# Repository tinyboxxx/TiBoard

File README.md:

# TiBoard
>  TiBoard的硬件部分及说明文件

- merged SofleKeyboard and nrfBoard
- reserved place for trackpoint
- position of keys moved to my hand measurements
- carbon fiber top plate
- Voronoi style 3D print keycap

打包的KiCAD如果有什么问题麻烦发issue。

## 许可

可以自己随便做着玩。

空板交易无所谓，不要闲鱼卖套件，不要卖成品。

转载和修改版请带上我的名字。

## 需要注意购买的零件

**注意：为单套，左右手两只的数量需要x2 ！**

| 项目                 | 备注                                                         | 数量（单个板） | 链接                                                         |
| -------------------- | ------------------------------------------------------------ | -------------- | ------------------------------------------------------------ |
| E73蓝牙模块（PCB内） | E73-2G4M08S1C                                                | 1              | https://m.tb.cn/h.UL6DjRC  亿佰特nRF52840/52833芯片无线蓝牙MESH模块BLE4.2/5.0陶瓷天线 |
| 锂电池               | 402030（长30宽20厚4）不一定非要这家店，同尺寸带保护板即可。  | 1              | https://m.tb.cn/h.Upcs7Os  伯朗 导航行车记录仪锂电池大容量通用3.7v聚合物 |
| 轴体                 | 必须凯华1350型号，颜色任选                                   | 30             | https://m.tb.cn/h.UK0Awu7  凯华Kailh 1350巧克力机械键盘轴体  |
| 轴体热插拔底座       | 必须凯华1350型号                                             | 30             | https://item.taobao.com/item.htm?id=667154671807             |
| 定位板               | 厚度1.2mm，dxf文件见附件，参考价格碳纤维RMB68两片。也可以使用玻纤等其他不导电材料。 | 1              | https://item.taobao.com/item.htm?id=40340403528              |

## 状态及已知问题

BOM里充电电流设定用的R9 现在用的是2.2K，二极管是1N4148WS。

有其他疑问也请发issue。

已知问题：

- 目前使用的电池功耗大约1至2天，建议随时充电。
- 键位比较少 符号和其他按键不大方便。
- reset按钮位置比较难按。
- USB Type-C接口没有做沉板，左手的接口比较靠近桌子。
- 电池接插件比较大，目前直接焊线。
- I2C的两个电阻实测可以不焊接。
- 烧录E73模块真的很麻烦，需要先刷ST-LINK的固件 或者用STM32
- 指点杆的安装比较麻烦，而且可能影响厚度，兼容性还未测试。

## 链接

固件 https://github.com/tinyboxxx/zmk-config

固件下载 https://github.com/tinyboxxx/zmk-config/actions

键位编辑器 [ZMK Keymap Editor (nickcoutsos.github.io)](https://nickcoutsos.github.io/keymap-editor/)

视频 https://www.bilibili.com/video/BV1qe4y1t7zE/

烧录bootloader https://github.com/joric/nrfmicro/wiki/Bootloader#nrf52840

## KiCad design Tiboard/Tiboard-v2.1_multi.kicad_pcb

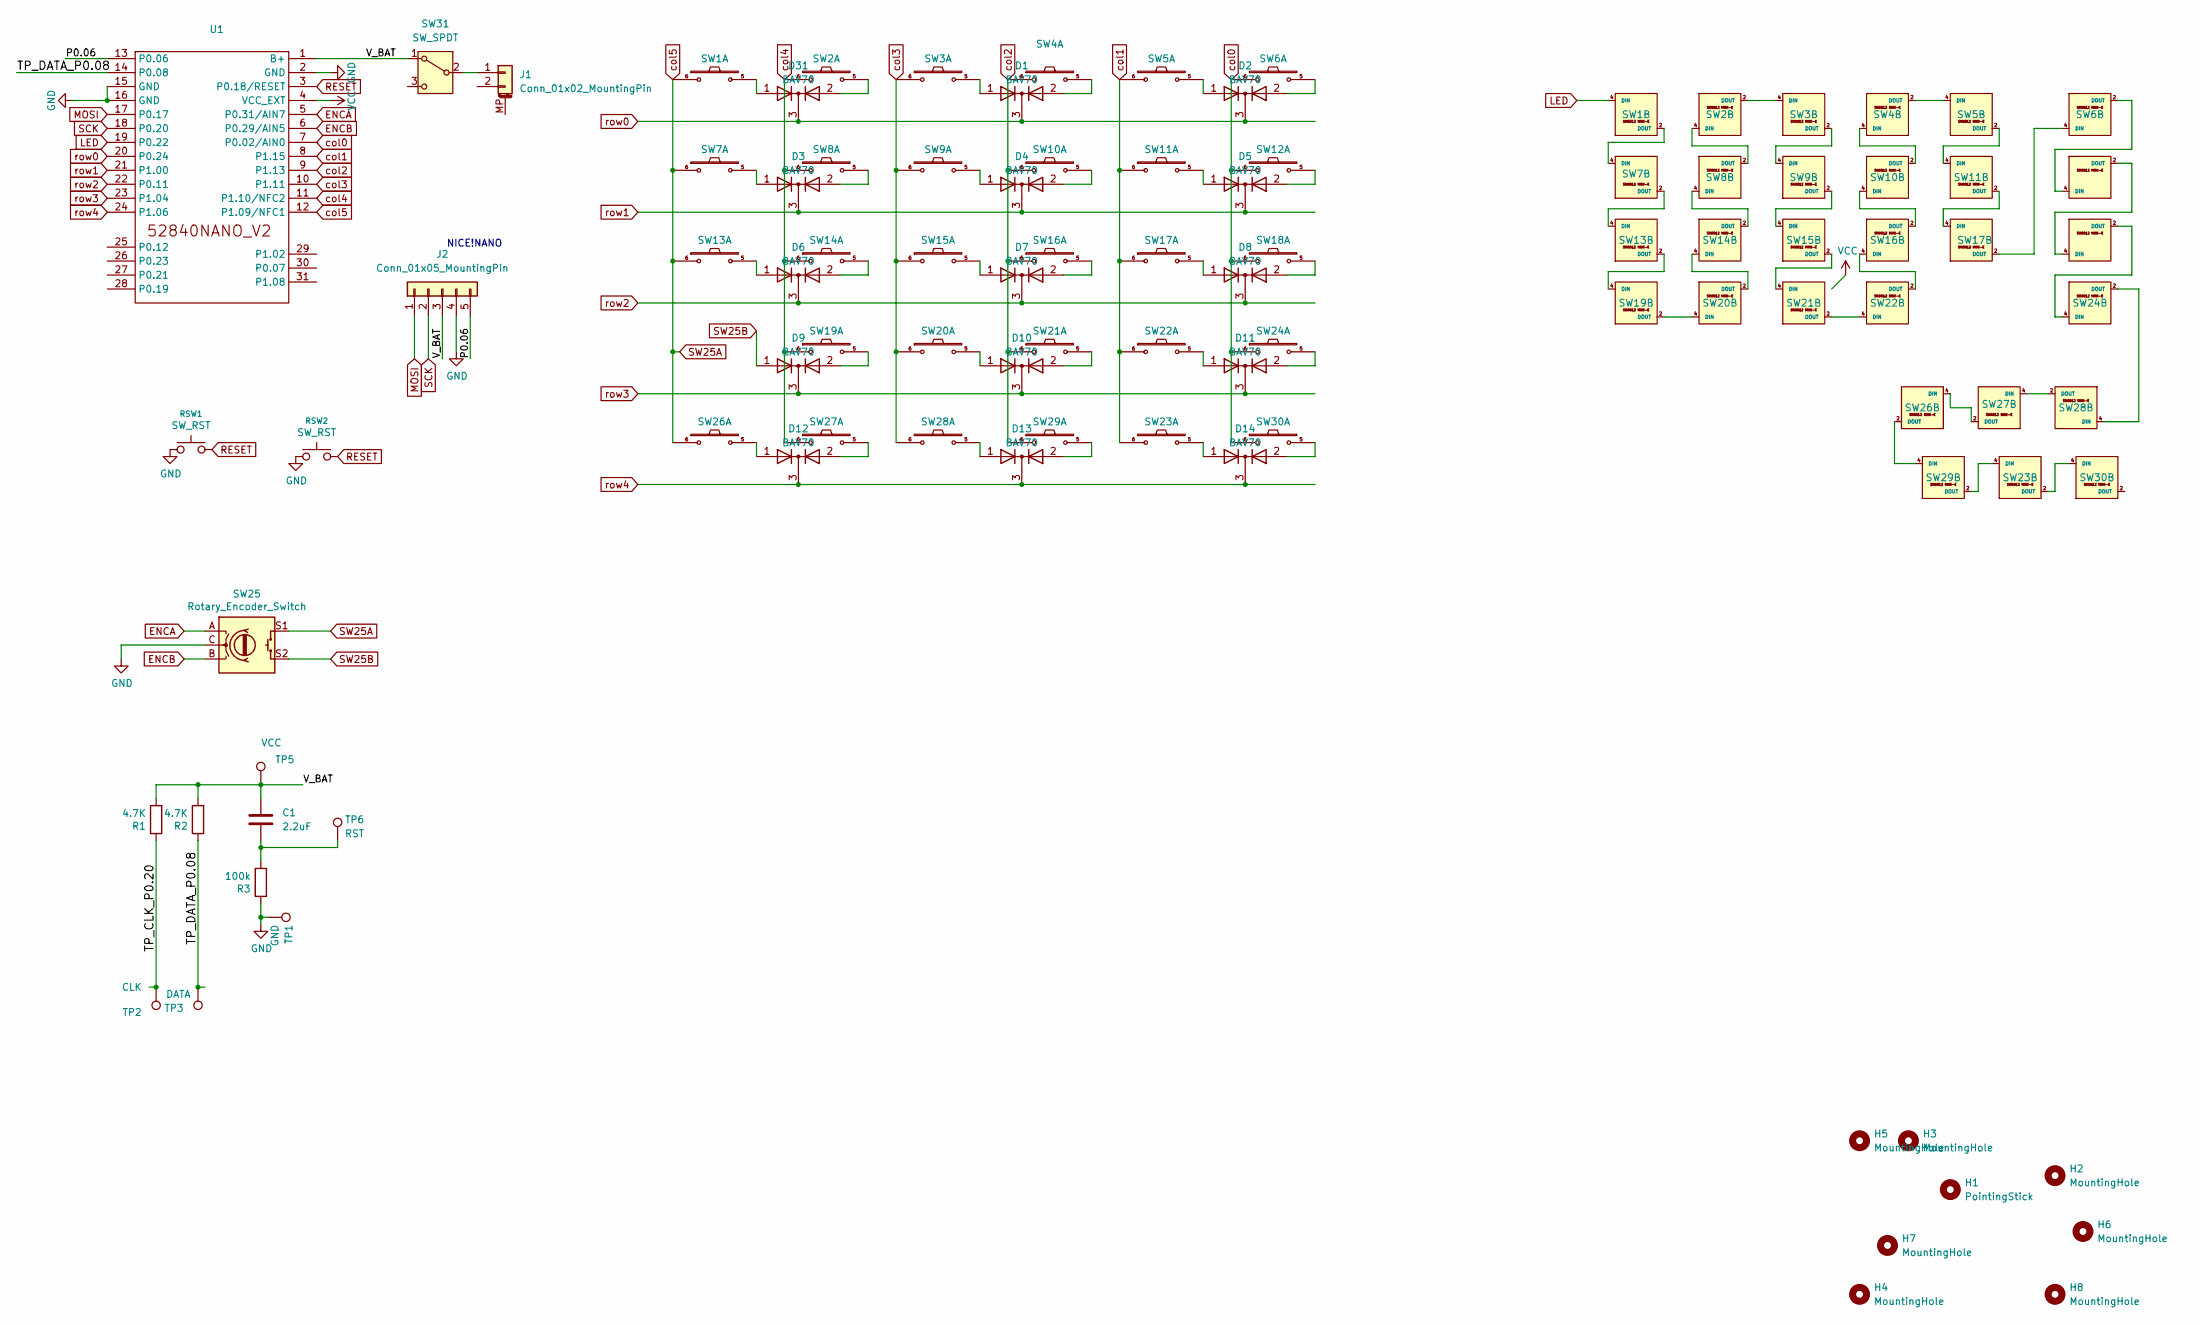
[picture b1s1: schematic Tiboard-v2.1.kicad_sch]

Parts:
C1: 2.2uF; C_0603_1608Metric
D1, D2, D3, D4, D5, D6, D7, D8, D9, D10, D11, D12, D13, D14, D31: BAV70; SOT-23
H1: PointingStick; Pointing_Stick
H2, H3, H4, H5, H6, H7, H8: MountingHole; MountingHole_3.2mm_M3_Pad_Via
J1: Conn_01x02_MountingPin; JST_SHL_SM02B-SHLS-TF_1x02-1MP_P1.00mm_Horizontal
J2: Conn_01x05_MountingPin; NICEVIEW_5Pin
R1, R2: 4.7K; R_0603_1608Metric
R3: 100k; R_0603_1608Metric
RSW1, RSW2: SW_RST; SW_SPST_CK_KXT3
SW1, SW2, SW3, SW4, SW5, SW6, SW7, SW8, SW9, SW10, SW11, SW12, SW13, SW14, SW15, SW16, SW17, SW18, SW19, SW20, SW21, SW22, SW23, SW24, SW26, SW27, SW28, SW29, SW30: SW_PUSH_LED; TTC_mini
SW25: Rotary_Encoder_Switch; RotaryEncoder_Alps_EC11E-Switch_Vertical_H20mm-keebio_modif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
SW31: SW_SPDT; SW_Slide_SPDT_Angled_CK_OS102011MA1Q
TP1: GND; TestPoint_Pad_1.0x1.0mm
TP2: CLK; TestPoint_Pad_1.0x1.0mm
TP3: DATA; TestPoint_Pad_1.0x1.0mm
TP5: VCC; TestPoint_Pad_1.0x1.0mm
TP6: RST; TestPoint_Pad_1.0x1.0mm
U1: 52840NANO_V2

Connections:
/P0.06: J2.5, U1.13 (P0.06)
ENCA: SW25.A, U1.5 (P0.31/AIN7)
ENCB: SW25.B, U1.6 (P0.29/AIN5)
LED: SW1.4 (DIN), U1.19 (P0.22)
unnamed: C1.2, R3.2, TP6.1
unnamed: D1.1 (A), SW3.5
unnamed: D1.2 (A), SW4.5
unnamed: D2.1 (A), SW5.5
unnamed: D2.2 (A), SW6.5
unnamed: D3.1 (A), SW7.5
unnamed: D3.2 (A), SW8.5
unnamed: D4.1 (A), SW9.5
unnamed: D4.2 (A), SW10.5
unnamed: D5.1 (A), SW11.5
unnamed: D5.2 (A), SW12.5
unnamed: D6.1 (A), SW13.5
unnamed: D6.2 (A), SW14.5
unnamed: D7.1 (A), SW15.5
unnamed: D7.2 (A), SW16.5
unnamed: D8.1 (A), SW17.5
unnamed: D8.2 (A), SW18.5
unnamed: D9.2 (A), SW19.5
unnamed: D10.1 (A), SW20.5
unnamed: D10.2 (A), SW21.5
unnamed: D11.1 (A), SW22.5
unnamed: D11.2 (A), SW24.5
unnamed: D12.1 (A), SW26.5
unnamed: D12.2 (A), SW27.5
unnamed: D13.1 (A), SW28.5
unnamed: D13.2 (A), SW29.5
unnamed: D14.1 (A), SW23.5
unnamed: D14.2 (A), SW30.5
unnamed: D31.1 (A), SW1.5
unnamed: D31.2 (A), SW2.5
unnamed: J1.1, SW31.2 (B)
unnamed: SW1.2 (DOUT), SW7.4 (DIN)
unnamed: SW2.4 (DIN), SW8.2 (DOUT)
unnamed: SW2.2 (DOUT), SW3.4 (DIN)
unnamed: SW3.2 (DOUT), SW9.4 (DIN)
unnamed: SW4.2 (DOUT), SW5.4 (DIN)
unnamed: SW10.4 (DIN), SW16.2 (DOUT)
unnamed: SW4.4 (DIN), SW10.2 (DOUT)
unnamed: SW5.2 (DOUT), SW11.4 (DIN)
unnamed: SW11.2 (DOUT), SW17.4 (DIN)
unnamed: SW6.2 (DOUT), SW12.4 (DIN)
unnamed: SW12.2 (DOUT), SW18.4 (DIN)
unnamed: SW7.2 (DOUT), SW13.4 (DIN)
unnamed: SW13.2 (DOUT), SW19.4 (DIN)
unnamed: SW14.4 (DIN), SW20.2 (DOUT)
unnamed: SW8.4 (DIN), SW14.2 (DOUT)
unnamed: SW9.2 (DOUT), SW15.4 (DIN)
unnamed: SW15.2 (DOUT), SW21.4 (DIN)
unnamed: SW16.4 (DIN), SW22.2 (DOUT)
unnamed: SW6.4 (DIN), SW17.2 (DOUT)
unnamed: SW18.2 (DOUT), SW24.4 (DIN)
unnamed: SW19.2 (DOUT), SW20.4 (DIN)
unnamed: SW21.2 (DOUT), SW22.4 (DIN)
unnamed: SW23.4 (DIN), SW29.2 (DOUT)
unnamed: SW23.2 (DOUT), SW30.4 (DIN)
unnamed: SW24.2 (DOUT), SW28.4 (DIN)
unnamed: SW26.4 (DIN), SW27.2 (DOUT)
unnamed: SW26.2 (DOUT), SW29.4 (DIN)
unnamed: SW27.4 (DIN), SW28.2 (DOUT)
RESET: RSW1.2, RSW2.2, U1.3 (P0.18/RESET)
SCL: J2.2, U1.18 (P0.20)
SDA: J2.1, U1.17 (P0.17)
SW25A: SW1.6, SW7.6, SW13.6, SW25.S1, SW26.6, U1.12 (P1.09/NFC1)
SW25B: D9.1 (A), SW25.S2
VCC: SW1.1 (VDD), SW2.1 (VDD), SW3.1 (VDD), SW4.1 (VDD), SW5.1 (VDD), SW6.1 (VDD), SW7.1 (VDD), SW8.1 (VDD), SW9.1 (VDD), SW10.1 (VDD), SW11.1 (VDD), SW12.1 (VDD), SW13.1 (VDD), SW14.1 (VDD), SW15.1 (VDD), SW16.1 (VDD), SW17.1 (VDD), SW18.1 (VDD), SW19.1 (VDD), SW20.1 (VDD), SW21.1 (VDD), SW22.1 (VDD), SW23.1 (VDD), SW24.1 (VDD), SW26.1 (VDD), SW27.1 (VDD), SW28.1 (VDD), SW29.1 (VDD), SW30.1 (VDD), U1.4 (VCC_EXT)
col0: SW6.6, SW12.6, SW18.6, SW24.6, SW30.6, U1.7 (P0.02/AIN0)
col1: SW5.6, SW11.6, SW17.6, SW22.6, SW23.6, U1.8 (P1.15)
col2: SW4.6, SW10.6, SW16.6, SW21.6, SW29.6, U1.9 (P1.13)
col3: SW3.6, SW9.6, SW15.6, SW20.6, SW28.6, U1.10 (P1.11)
col4: SW2.6, SW8.6, SW14.6, SW19.6, SW27.6, U1.11 (P1.10/NFC2)
row0: D1.3 (K), D2.3 (K), D31.3 (K), U1.20 (P0.24)
row1: D3.3 (K), D4.3 (K), D5.3 (K), U1.21 (P1.00)
row2: D6.3 (K), D7.3 (K), D8.3 (K), U1.22 (P0.11)
row3: D9.3 (K), D10.3 (K), D11.3 (K), U1.23 (P1.04)
row4: D12.3 (K), D13.3 (K), D14.3 (K), U1.24 (P1.06)

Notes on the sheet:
NICE!NANO

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
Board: 2 copper layers, 71 parts (9 on the bottom side), 83 nets, no tracks yet.

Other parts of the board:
TP4: DATA; TestPoint_Pad_1.0x1.0mm
TP7: GND; TestPoint_Pad_1.0x1.0mm
kibuzzard-62E281FD: G***; kibuzzard-62E281FD

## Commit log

2022-09-23 gerber added
    从华秋下载下来的gerber
2022-09-23 file update
    顶板目前有点紧 安装比较麻烦
2022-10-12 开源上传
2022-10-12 readme update
2023-03-01 BOM added
2024-07-28 Tiboard V2 developing
2024-07-28 day1 for Tiboard V2
